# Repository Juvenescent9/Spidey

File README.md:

# Spidey
A 3x3 macropad designed to resemble a spider

When designing, I took inspiration from the Mercury k1 keyboard made by Gravastar. It is a 9 key macropad, using the XIAO RP2040 microcontroller and powered with KMK firmware. It has 6 articulated limbs that can be adjusted to change the position of the macropad, but mostly because of design preferences. 

# CAD design

The design was fully created in Fusion 360. The case is held by 4 M3 16mm screws, and has 3 plates for the frame. The limbs are made with a ball and socket joint and can allow the macropad to be tilted or even lifted!  _**Although in the CAD file, the limbs are displayed as passing through the framework, when actually built it will be held by printing the limbs individually, and then securing them on accordingly with a 3d pen or hotglue. This is extrememely important for assembly**_ All essential parts of the casing can be printed without supports, except the legs which are not needed for functional reasons and are optional.

Hackpad without limbs

# PCB
The PCB was made in Kicad. I used a traditional 6 pin system.

# Firmware
The hackpad uses KMK firmware.

# BOM
Solder, PCB, motivation, and caffeine not included, but required

## Electronic parts
 - 9 DSA keycaps
 - 9 1n4148 diodes
 - 1 XIAO RP2040 (with headers)
 - 9 Cherry MX switches

## Case
 - 4 M3x16mm screws
 - Top part of case
 - Middle part of case
 - Bottom of case
 - 6-8 spider limbs (Optional, number depends on preference)
 - 3d pen (Optional, for securing limbs)
 - Hot glue (Optional, for grip)

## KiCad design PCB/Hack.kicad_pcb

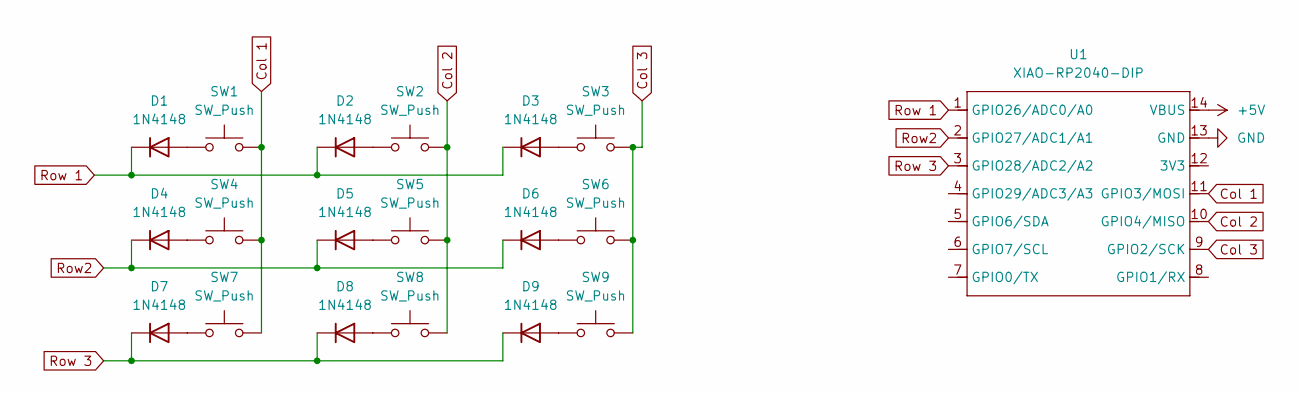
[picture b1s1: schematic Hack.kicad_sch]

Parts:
D1, D2, D3, D4, D5, D6, D7, D8, D9: 1N4148; D_DO-35_SOD27_P7.62mm_Horizontal
SW1, SW2, SW3, SW4, SW5, SW6, SW7, SW8, SW9: SW_Push; SW_Cherry_MX_1.00u_PCB
U1: XIAO-RP2040-DIP

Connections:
+5V: U1.14 (VBUS)
Col 1: SW1.2, SW4.2, SW7.2, U1.11 (GPIO3/MOSI)
Col 2: SW2.2, SW5.2, SW8.2, U1.10 (GPIO4/MISO)
Col 3: SW3.2, SW6.2, SW9.2, U1.9 (GPIO2/SCK)
GND: U1.13 (GND)
unnamed: D1.2 (A), SW1.1
unnamed: D2.2 (A), SW2.1
unnamed: D3.2 (A), SW3.1
unnamed: D4.2 (A), SW4.1
unnamed: D5.2 (A), SW5.1
unnamed: D6.2 (A), SW6.1
unnamed: D7.2 (A), SW7.1
unnamed: D8.2 (A), SW8.1
unnamed: D9.2 (A), SW9.1
Row2: D4.1 (K), D5.1 (K), D6.1 (K), U1.2 (GPIO27/ADC1/A1)
Row 1: D1.1 (K), D2.1 (K), D3.1 (K), U1.1 (GPIO26/ADC0/A0)
Row 3: D7.1 (K), D8.1 (K), D9.1 (K), U1.3 (GPIO28/ADC2/A2)

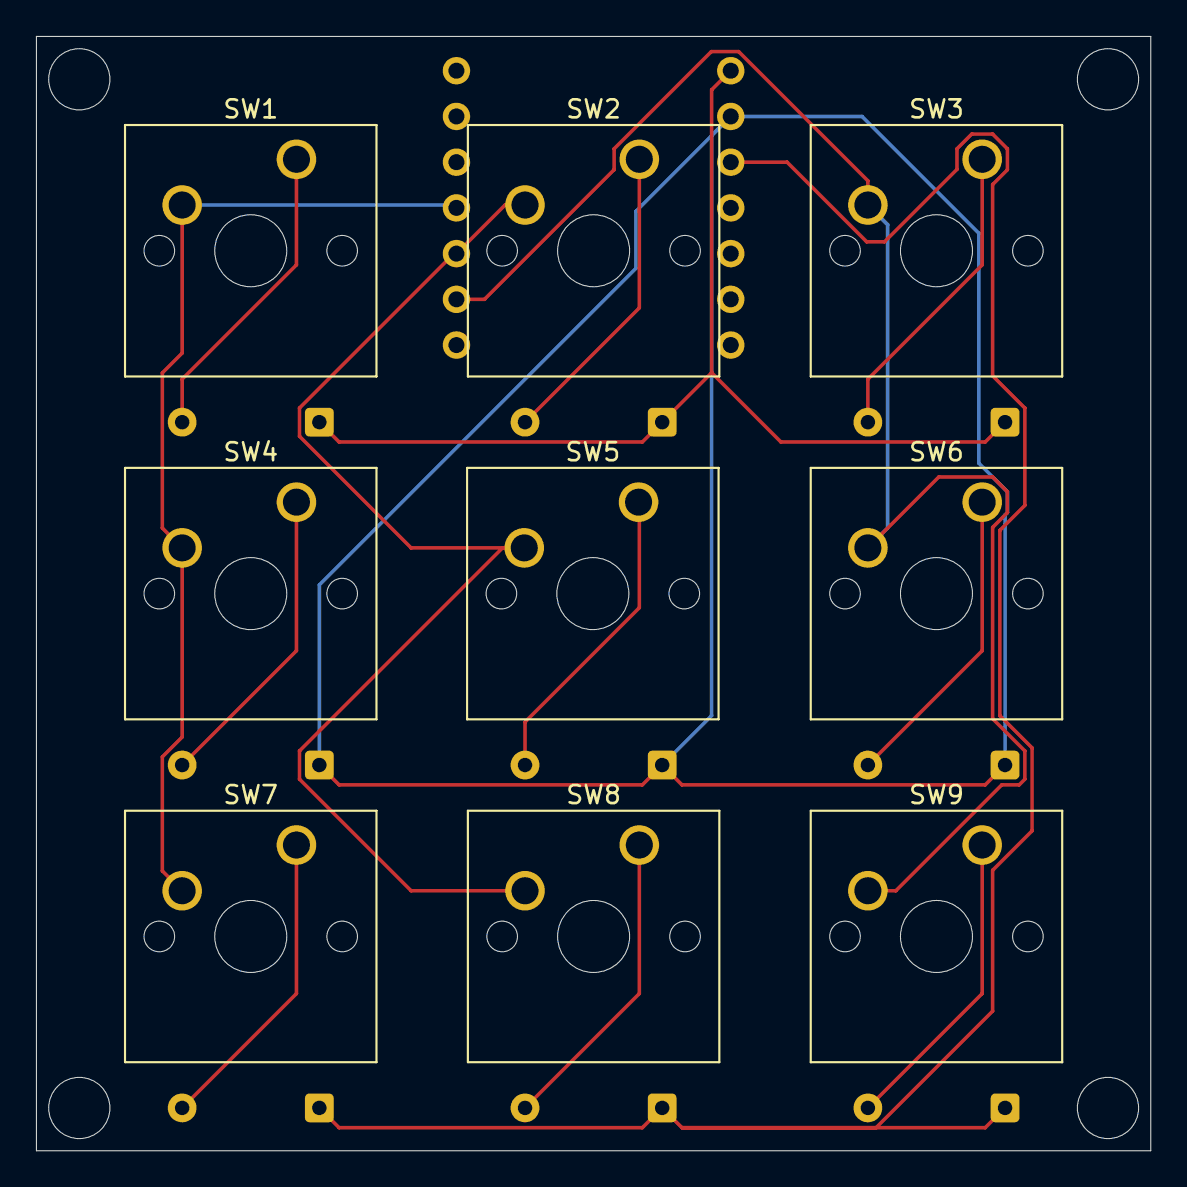
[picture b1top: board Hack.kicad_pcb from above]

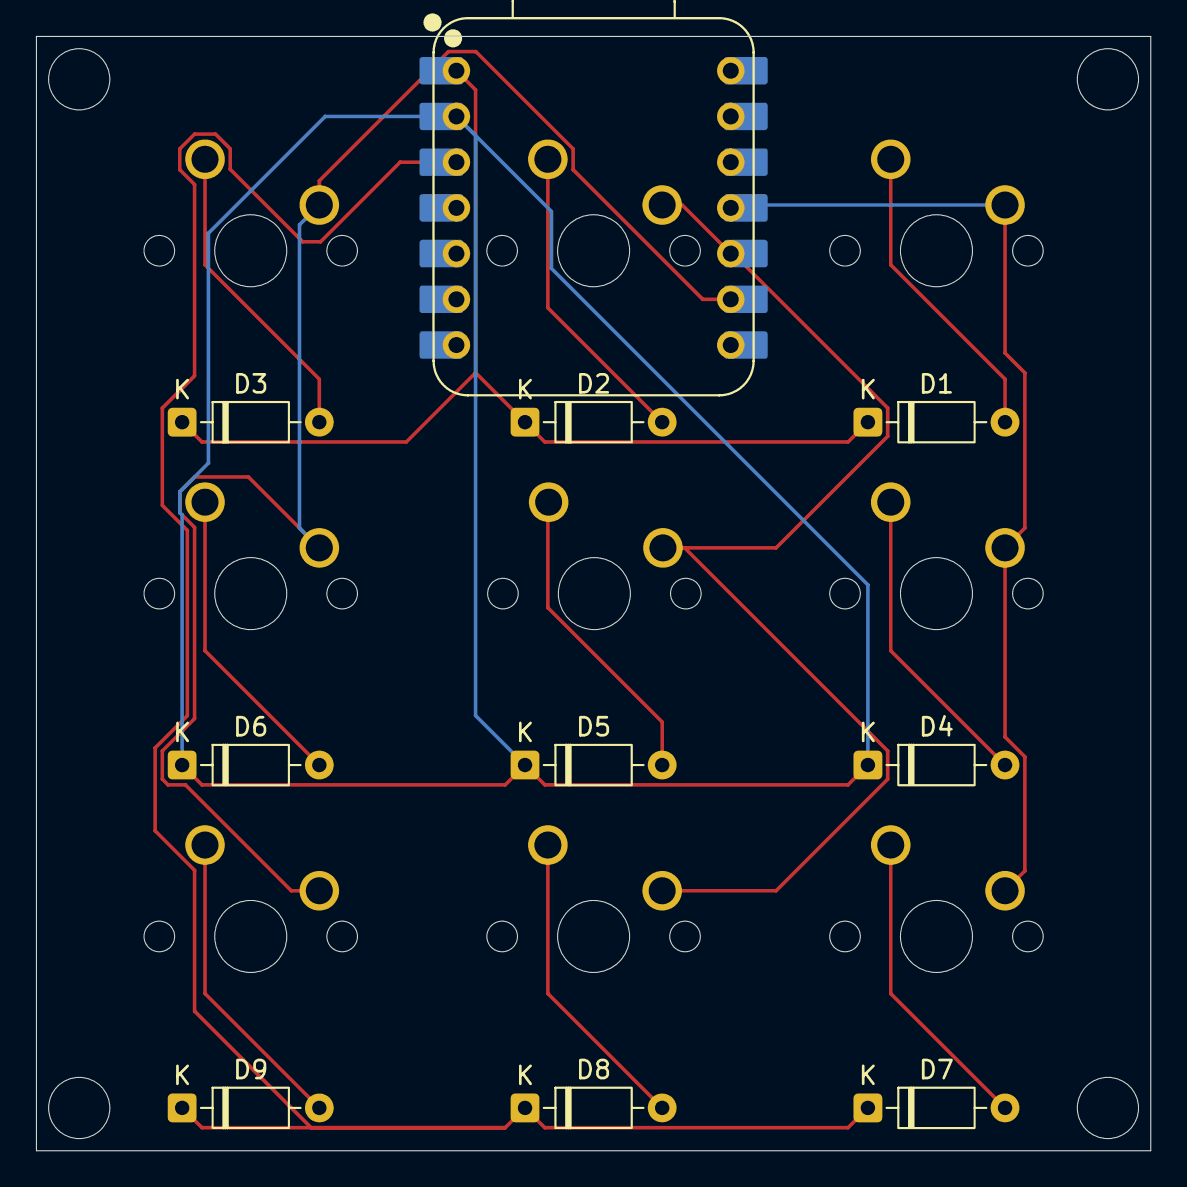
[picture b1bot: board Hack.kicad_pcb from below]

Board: 2 copper layers, 61.9 x 61.9 mm, 19 parts (10 on the bottom side), 15 nets.

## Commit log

2025-06-24 Create CAD
2025-06-24 Create PCB
2025-06-24 Create Firmware
2025-06-24 Create Images
2025-06-24 Create Journal
2025-06-25 Rename Hackpad v5.step to FullDesignHackpad.step
    This is the full design of the hacked
2025-06-25 This is the full hackpad design w all parts
2025-06-25 Create a
2025-06-25 Create kmk
2025-06-25 Rename kmk to main.py
2025-06-25 Create empty file
